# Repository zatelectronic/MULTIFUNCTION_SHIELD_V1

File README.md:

<div align="center">

# MULTIFUNCTION SHIELD V1

**Shield multifuncional para Arduino Uno com LEDs, botões, buzzer, potenciômetro, LDR, conector I2C e borne de terminais — tudo em uma única placa de expansão**

</div>

---

## 📋 Índice

- [MULTIFUNCTION SHIELD V1](#multifunction-shield-v1)
  - [📋 Índice](#-índice)
  - [Visão Geral](#visão-geral)
  - [Renders 3D](#renders-3d)
  - [Funcionalidades](#funcionalidades)
  - [Mapa de Pinos](#mapa-de-pinos)
  - [Especificações Técnicas](#especificações-técnicas)
  - [Lista de Materiais](#lista-de-materiais)
  - [Aplicações](#aplicações)
  - [Estrutura do Repositório](#estrutura-do-repositório)
  - [Como Usar](#como-usar)
    - [Instalação](#instalação)
    - [Exemplo — Piscar os 4 LEDs em sequência](#exemplo--piscar-os-4-leds-em-sequência)
    - [Exemplo — Leitura do potenciômetro e LDR](#exemplo--leitura-do-potenciômetro-e-ldr)
    - [Exemplo — Botões com pull-down](#exemplo--botões-com-pull-down)
  - [Sobre](#sobre)

---

## Visão Geral

**MULTIFUNCTION SHIELD V1** é uma placa de expansão (shield) para **Arduino Uno R3**, projetada pela **ZAT ELECTRONIC** utilizando **KiCad 10**. O shield encaixa diretamente nos conectores do Arduino e disponibiliza um conjunto completo de periféricos prontos para uso imediato em projetos de aprendizado, prototipagem e experimentos com eletrônica e programação.

Em uma única placa são integrados: **4 LEDs coloridos**, **4 botões tácteis**, **1 buzzer**, **1 potenciômetro**, **1 sensor LDR**, **1 conector I2C** (GND / VCC / SDA / SCL) e **1 borne de terminais** — cobrindo as principais necessidades de entrada e saída para projetos com Arduino.

> 💡 Ideal para aulas, workshops, laboratórios maker e iniciantes em eletrônica e programação com Arduino.

---

## Renders 3D

<div align="center">

*Vista superior — LEDs coloridos, botões tácteis, buzzer, potenciômetro e LDR*

<br/>

*Vista isométrica frontal — pinout Arduino Uno R3 e conector I2C*

<br/>

*Vista isométrica traseira — borne de terminais, pinos analógicos e digitais*

</div>

---

## Funcionalidades

- ✅ **4 LEDs 5mm PTH** — azul (LED1), vermelho (LED2), verde (LED3) e amarelo (LED4)
- ✅ **4 botões tácteis** (SW1–SW4) — 6×6×5mm PTH, com resistores pull-up 10KΩ (ativos em nível baixo)
- ✅ **1 buzzer PTH** (BZ1) — sinalização sonora ativa
- ✅ **1 potenciômetro 10KΩ** (RV1) — entrada analógica ajustável
- ✅ **1 sensor LDR** (R2) — leitura de luminosidade ambiente (divisor com R1 10KΩ)
- ✅ **1 conector I2C** (J2 — 4 pinos: GND / VCC / SDA / SCL) — expansão para displays, sensores e módulos I2C
- ✅ **1 borne de terminais KRE 3 pinos** (J1 — D11 / D12 / GND) — conexão externa por parafuso
- ✅ **Resistores de proteção 220Ω** (R7–R11) — para os LEDs e buzzer
- ✅ **Resistores pull-up 10KΩ** (R1, R3–R6) — para LDR e botões
- ✅ **Encaixe direto** no Arduino Uno R3 — sem soldagem adicional no Arduino
- ✅ **Todos os componentes PTH** — montagem manual simples
- ✅ **Made in Brazil** — serigrafia na PCB

---

## Mapa de Pinos

| Periférico | Pino Arduino | Descrição |
|------------|-------------|-----------|
| **LED1** — LED Azul | D2 | Saída digital |
| **LED2** — LED Vermelho | D3 | Saída digital (PWM) |
| **LED3** — LED Verde | D4 | Saída digital |
| **LED4** — LED Amarelo | D5 | Saída digital (PWM) |
| **SW1** — Botão 1 | D6 | Entrada digital (LOW = pressionado) |
| **SW2** — Botão 2 | D7 | Entrada digital (LOW = pressionado) |
| **SW3** — Botão 3 | D8 | Entrada digital (LOW = pressionado) |
| **SW4** — Botão 4 | D9 | Entrada digital (LOW = pressionado) |
| **BZ1** — Buzzer | D10 | Saída digital (PWM) |
| **RV1** — Potenciômetro | A0 | Entrada analógica |
| **R2** — Sensor de luz (LDR) | A1 | Entrada analógica |
| **J2 SDA** — I2C Dados | A4 (SDA) | Comunicação I2C |
| **J2 SCL** — I2C Clock | A5 (SCL) | Comunicação I2C |
| **J1** — Borne | D11 / D12 / GND | Terminal externo |

---

## Especificações Técnicas

| Parâmetro | Valor |
|-----------|-------|
| **Compatibilidade** | Arduino Uno R3 (encaixe direto) |
| **LEDs** | 4x 5mm PTH — azul, vermelho, verde, amarelo |
| **Botões** | 4x tácteis 6×6×5mm PTH |
| **Buzzer** | 1x PTH ativo |
| **Potenciômetro** | 1x 10KΩ PTH |
| **Sensor de Luz** | 1x LDR PTH |
| **Conector I2C** | 1x header 4 pinos 2,54mm (GND / VCC / SDA / SCL) |
| **Borne de Terminais** | 1x KRE 3 pinos, passo 5,0mm (D11 / D12 / GND) |
| **Resistores LEDs/Buzzer** | 220Ω — R7, R8, R9, R10, R11 |
| **Resistores Pull-up** | 10KΩ — R1 (LDR), R3, R4, R5, R6 (botões) |
| **Tensão de operação** | 5V (alimentado pelo Arduino) |
| **Tipo de montagem** | PTH — Através-furo |
| **Ferramenta de Projeto** | KiCad 10 |
| **Versão** | V1 — 2025 |

---

## Lista de Materiais

| Ref | Componente | Valor / Cor | Encapsulamento |
|-----|-----------|------------|----------------|
| A1 | Arduino Uno R3 | — | Shield (encaixe) |
| LED1 | LED 5mm | Azul | PTH 5mm |
| LED2 | LED 5mm | Vermelho | PTH 5mm |
| LED3 | LED 5mm | Verde | PTH 5mm |
| LED4 | LED 5mm | Amarelo | PTH 5mm |
| SW1–SW4 | Botão Táctil | 6×6×5mm | PTH |
| BZ1 | Buzzer | Ativo | PTH |
| RV1 | Potenciômetro | 10KΩ | PTH |
| R2 | Sensor de Luz (LDR) | LDR 5mm | PTH Vertical |
| J1 | Borne de Terminais | D11 / D12 / GND | KRE 3 pinos 5,0mm |
| J2 | Conector I2C | GND / VCC / SDA / SCL | Header 4 pinos 2,54mm |
| R7, R8, R9, R10, R11 | Resistor de proteção | 220Ω | Axial DIN0204 PTH |
| R1, R3, R4, R5, R6 | Resistor pull-up | 10KΩ | Axial DIN0204 PTH |

---

## Aplicações

- 🎓 **Ensino de eletrônica e programação** — plataforma completa para aprender Arduino do zero
- 🔬 **Prototipagem rápida** — periféricos prontos sem necessidade de protoboard
- 🏫 **Laboratórios maker e escolas técnicas** — kit de experimentos em uma única placa
- 🎮 **Projetos interativos** — jogos, quizzes e desafios com LEDs e botões
- 📡 **Integração com módulos I2C** — displays OLED, sensores de temperatura, RTC, etc.
- 🔊 **Projetos sonoros** — alarmes, melodias e sinalizações com buzzer
- 🌅 **Automação com luz** — controle baseado em luminosidade via LDR

---

## Estrutura do Repositório

```
MULTIFUNCTION_SHIELD_V1/
├── MULTIFUNCTION_SHIELD_V1.kicad_pro        # Arquivo de projeto KiCad
├── MULTIFUNCTION_SHIELD_V1.kicad_sch        # Esquemático: capa A2 + folhas ARDUINO / ENTRADAS / SAIDAS (KiCad 10)
├── MULTIFUNCTION_SHIELD_V1.kicad_pcb        # Layout da PCB (KiCad 10)
├── MULTIFUNCTION_SHIELD_V1.kicad_prl        # Configurações locais
├── packages3D/                              # Modelos 3D arquivados
│   ├── LED 5mm Blue.step
│   ├── LED 5mm Red.step
│   ├── LED 5mm Green.step
│   ├── LED 5mm Yellow.step
│   ├── SW_PUSH_6mm_H5mm.wrl
│   ├── Buzzer_12x9.5RM7.6.wrl
│   ├── Rez10K.stp
│   ├── R_LDR_5.1x4.3mm_P3.4mm_Vertical.wrl
│   ├── DG306-5.0-03P-12-00AH.STEP
│   ├── PinHeader_1x04_P2.54mm_Vertical.wrl
│   ├── SIL_Socket06_.stp
│   ├── SIL_Socket08_.stp
│   ├── SIL_Socket10_.stp
│   └── Resistor Axial 0.5W *.STEP
├── fp-info-cache                            # Cache de footprints
├── imagem_1.png                             # Render 3D superior
├── imagem_2.png                             # Render 3D isométrico frontal
├── imagem_3.png                             # Render 3D isométrico traseiro
└── README.md
```

---

## Como Usar

### Instalação

1. Encaixe o **MULTIFUNCTION SHIELD V1** diretamente nos conectores do Arduino Uno R3
2. Conecte o Arduino ao computador via USB
3. Abra a **Arduino IDE** ou **PlatformIO** e selecione a placa **Arduino Uno**
4. Carregue seu sketch e comece a experimentar

### Exemplo — Piscar os 4 LEDs em sequência

```cpp
#define LED_AZUL    2
#define LED_VERMELHO 3
#define LED_VERDE   4
#define LED_AMARELO 5

void setup() {
  pinMode(LED_AZUL,     OUTPUT);
  pinMode(LED_VERMELHO, OUTPUT);
  pinMode(LED_VERDE,    OUTPUT);
  pinMode(LED_AMARELO,  OUTPUT);
}

void loop() {
  digitalWrite(LED_AZUL, HIGH);    delay(300);
  digitalWrite(LED_AZUL, LOW);
  digitalWrite(LED_VERMELHO, HIGH); delay(300);
  digitalWrite(LED_VERMELHO, LOW);
  digitalWrite(LED_VERDE, HIGH);   delay(300);
  digitalWrite(LED_VERDE, LOW);
  digitalWrite(LED_AMARELO, HIGH); delay(300);
  digitalWrite(LED_AMARELO, LOW);
}
```

### Exemplo — Leitura do potenciômetro e LDR

```cpp
void setup() {
  Serial.begin(9600);
}

void loop() {
  int pot = analogRead(A0); // potenciômetro
  int ldr = analogRead(A1); // sensor de luz
  Serial.print("POT: "); Serial.print(pot);
  Serial.print(" | LDR: "); Serial.println(ldr);
  delay(500);
}
```

### Exemplo — Botões com pull-up (pressionado = LOW)

```cpp
#define BTN1 6
#define BTN2 7
#define BTN3 8
#define BTN4 9
#define BUZZER 10

void setup() {
  pinMode(BTN1, INPUT);
  pinMode(BTN2, INPUT);
  pinMode(BTN3, INPUT);
  pinMode(BTN4, INPUT);
  pinMode(BUZZER, OUTPUT);
}

void loop() {
  if (digitalRead(BTN1) == LOW) {
    tone(BUZZER, 1000, 200); // aciona buzzer ao pressionar SW1
  }
}
```

## Sobre

<div align="center">

Projetado por **ZAT ELECTRONIC**

*MULTIFUNCTION SHIELD V1 — 2025 — Made in Brazil 🇧🇷*

</div>

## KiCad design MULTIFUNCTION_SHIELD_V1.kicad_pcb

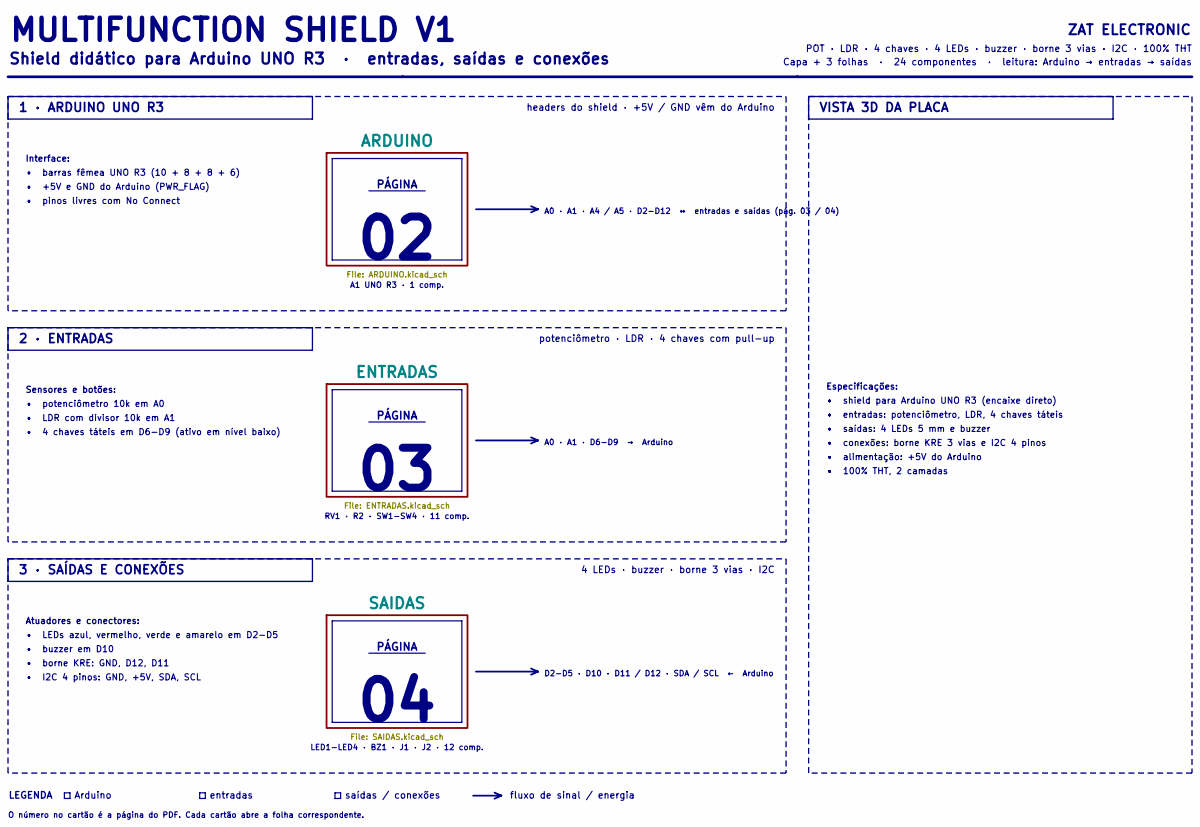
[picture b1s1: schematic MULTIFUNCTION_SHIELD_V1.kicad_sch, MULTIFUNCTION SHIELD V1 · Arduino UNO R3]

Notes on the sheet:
• saídas: 4 LEDs 5 mm e buzzer
headers do shield · +5V / GND vêm do Arduino
LED1-LED4 · BZ1 · J1 · J2 · 12 comp.
3 · SAÍDAS E CONEXÕES
potenciômetro · LDR · 4 chaves com pull-up
Arduino
• barras fêmea UNO R3 (10 + 8 + 8 + 6)
2 · ENTRADAS
• conexões: borne KRE 3 vias e I2C 4 pinos
PÁGINA
• alimentação: +5V do Arduino
saídas / conexões
Capa + 3 folhas · 24 componentes · leitura: Arduino → entradas → saídas
4 LEDs · buzzer · borne 3 vias · I2C
entradas
POT · LDR · 4 chaves · 4 LEDs · buzzer · borne 3 vias · I2C · 100% THT
LEGENDA
1 · ARDUINO UNO R3
• pinos livres com No Connect
• 100% THT, 2 camadas
• buzzer em D10
Especificações:
Shield didático para Arduino UNO R3 · entradas, saídas e conexões
• borne KRE: GND, D12, D11
VISTA 3D DA PLACA
A0 · A1 · D6-D9 → Arduino
• shield para Arduino UNO R3 (encaixe direto)
MULTIFUNCTION SHIELD V1
A1 UNO R3 · 1 comp.
Atuadores e conectores:
A0 · A1 · A4 / A5 · D2-D12 ↔ entradas e saídas (pág. 03 / 04)
• LEDs azul, vermelho, verde e amarelo em D2-D5
• I2C 4 pinos: GND, +5V, SDA, SCL
O número no cartão é a página do PDF. Cada cartão abre a folha correspondente.
• +5V e GND do Arduino (PWR_FLAG)
• entradas: potenciômetro, LDR, 4 chaves táteis
• LDR com divisor 10k em A1
• 4 chaves táteis em D6-D9 (ativo em nível baixo)
fluxo de sinal / energia
D2-D5 · D10 · D11 / D12 · SDA / SCL ← Arduino

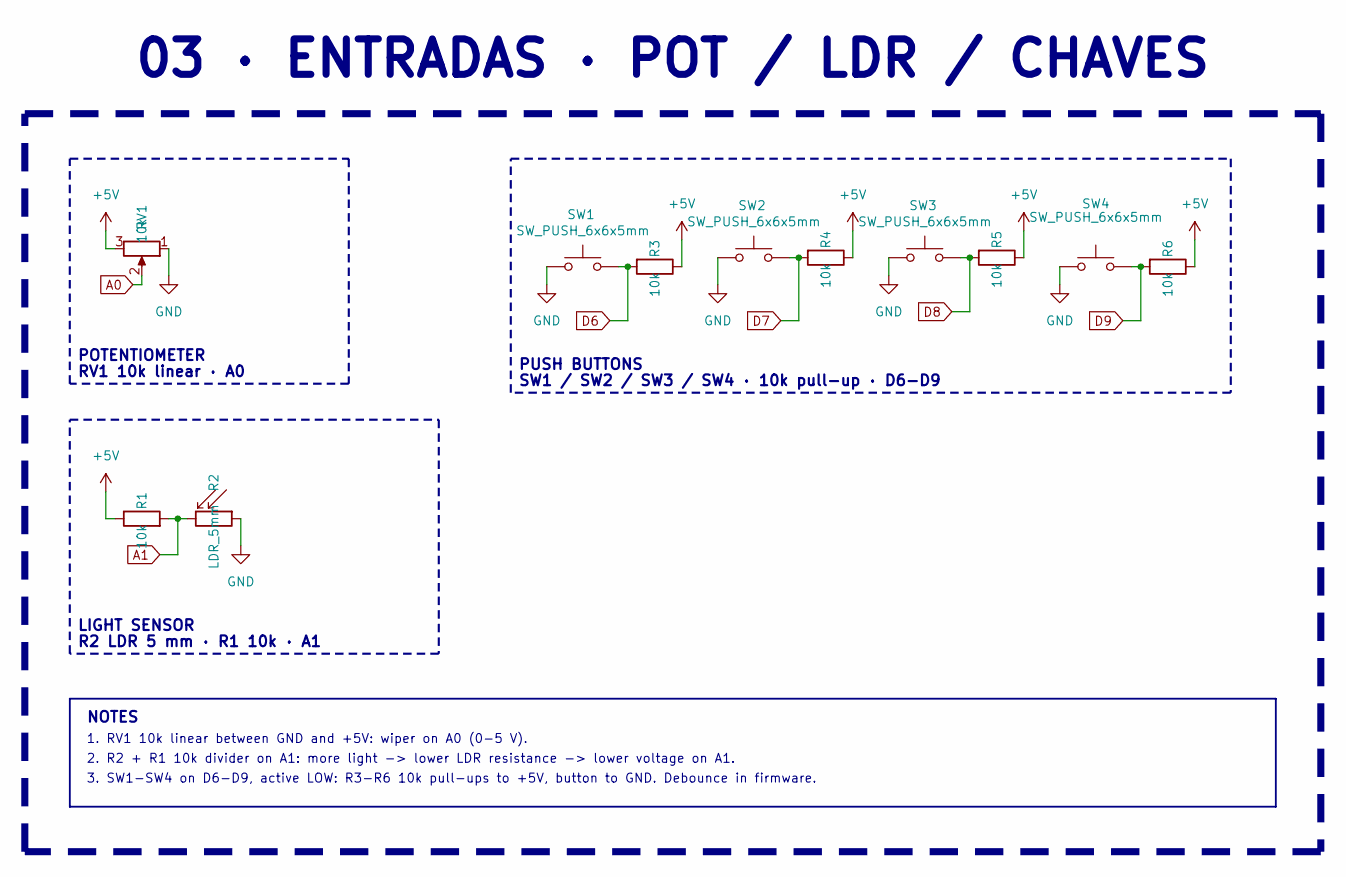
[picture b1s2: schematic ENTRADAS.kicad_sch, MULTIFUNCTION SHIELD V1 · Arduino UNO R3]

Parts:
R1, R3, R4, R5, R6: 10k; R_Axial_DIN0204_L3.6mm_D1.6mm_P7.62mm_Horizontal_10K
R2: LDR_5mm; R_LDR_5.1x4.3mm_P3.4mm_Vertical
RV1: 10k; Potentiometer_Piher_T-16H_Single_Horizontal_10K_EdgeMount
SW1, SW2, SW3, SW4: SW_PUSH_6x6x5mm; SW_PUSH_6mm_H5mm

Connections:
+5V: R1.1, R3.1, R4.1, R5.1, R6.1, RV1.3; also elsewhere on the board
A0: RV1.2; also elsewhere on the board
A1: R1.2, R2.2; also elsewhere on the board
D6: R3.2, SW1.2; also elsewhere on the board
D7: R4.2, SW2.2; also elsewhere on the board
D8: R5.2, SW3.2; also elsewhere on the board
D9: R6.2, SW4.2; also elsewhere on the board
GND: R2.1, RV1.1, SW1.1, SW2.1, SW3.1, SW4.1; also elsewhere on the board

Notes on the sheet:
1. RV1 10k linear between GND and +5V: wiper on A0 (0-5 V).
03 · ENTRADAS · POT / LDR / CHAVES
LIGHT SENSOR
R2 LDR 5 mm · R1 10k · A1
POTENTIOMETER
NOTES
PUSH BUTTONS
RV1 10k linear · A0
SW1 / SW2 / SW3 / SW4 · 10k pull-up · D6-D9
2. R2 + R1 10k divider on A1: more light -> lower LDR resistance -> lower voltage on A1.
3. SW1-SW4 on D6-D9, active LOW: R3-R6 10k pull-ups to +5V, button to GND. Debounce in firmware.

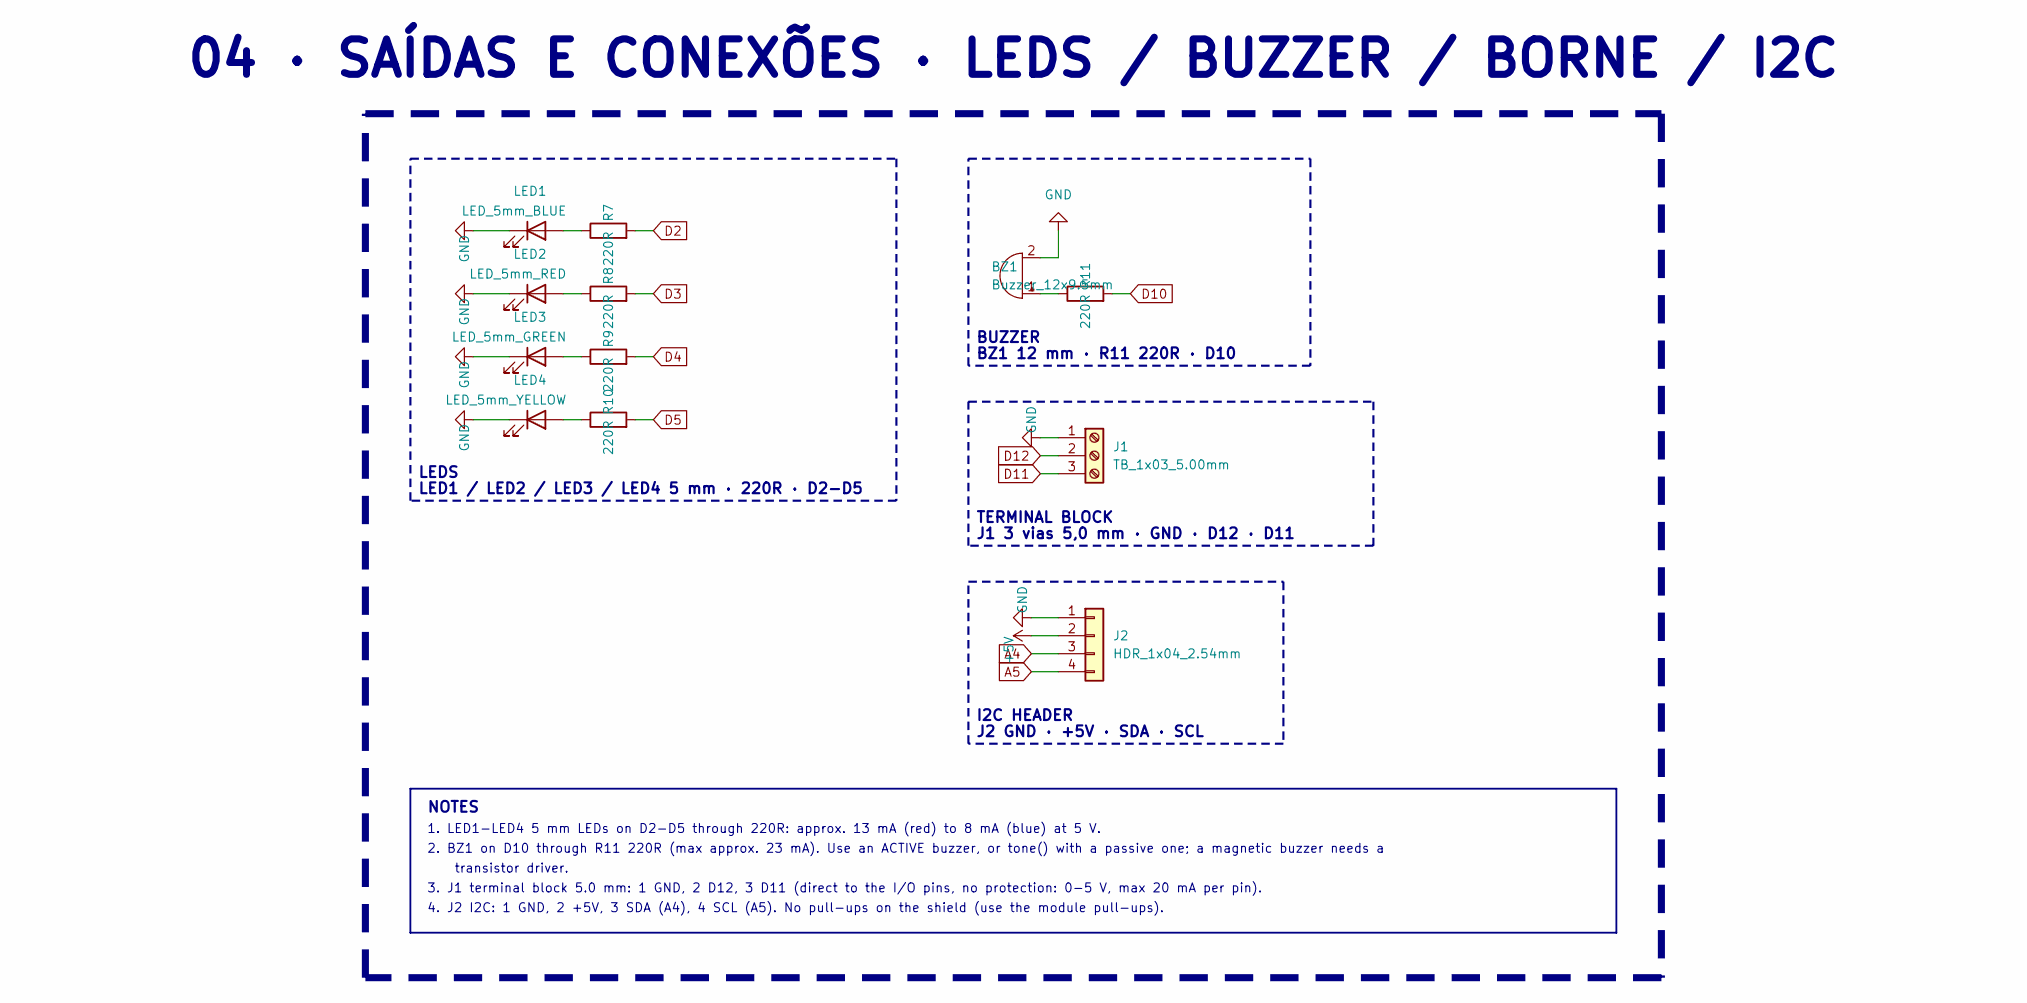
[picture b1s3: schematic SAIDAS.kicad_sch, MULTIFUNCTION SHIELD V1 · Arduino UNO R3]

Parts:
BZ1: Buzzer_12x9.5mm; Buzzer_12x9.5RM7.6
J1: TB_1x03_5.00mm; TerminalBlock_MaiXu_MX126-5.0-03P_1x03_P5.00mm_DG306
J2: HDR_1x04_2.54mm; PinHeader_1x04_P2.54mm_Vertical
LED1: LED_5mm_BLUE; LED_D5.0mm_Blue
LED2: LED_5mm_RED; LED_D5.0mm_Red
LED3: LED_5mm_GREEN; LED_D5.0mm_Green
LED4: LED_5mm_YELLOW; LED_D5.0mm_Yellow
R7, R8, R9, R10, R11: 220R; R_Axial_DIN0204_L3.6mm_D1.6mm_P7.62mm_Horizontal_220R

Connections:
+5V: J2.2; also elsewhere on the board
A4: J2.3; also elsewhere on the board
A5: J2.4; also elsewhere on the board
D2: R7.2; also elsewhere on the board
D3: R8.2; also elsewhere on the board
D4: R9.2; also elsewhere on the board
D5: R10.2; also elsewhere on the board
D10: R11.2; also elsewhere on the board
D11: J1.3; also elsewhere on the board
D12: J1.2; also elsewhere on the board
GND: BZ1.2 (-), J1.1, J2.1, LED1.1 (K), LED2.1 (K), LED3.1 (K), LED4.1 (K); also elsewhere on the board
unnamed: BZ1.1 (+), R11.1
unnamed: LED1.2 (A), R7.1
unnamed: LED2.2 (A), R8.1
unnamed: LED3.2 (A), R9.1
unnamed: LED4.2 (A), R10.1

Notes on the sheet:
J2 GND · +5V · SDA · SCL
TERMINAL BLOCK
BZ1 12 mm · R11 220R · D10
3. J1 terminal block 5.0 mm: 1 GND, 2 D12, 3 D11 (direct to the I/O pins, no protection: 0-5 V, max 20 mA per pin).
2. BZ1 on D10 through R11 220R (max approx. 23 mA). Use an ACTIVE buzzer, or tone() with a passive one; a magnetic buzzer needs a
I2C HEADER
4. J2 I2C: 1 GND, 2 +5V, 3 SDA (A4), 4 SCL (A5). No pull-ups on the shield (use the module pull-ups).
LED1 / LED2 / LED3 / LED4 5 mm · 220R · D2-D5
transistor driver.
J1 3 vias 5,0 mm · GND · D12 · D11
LEDS
BUZZER
NOTES
1. LED1-LED4 5 mm LEDs on D2-D5 through 220R: approx. 13 mA (red) to 8 mA (blue) at 5 V.
04 · SAÍDAS E CONEXÕES · LEDS / BUZZER / BORNE / I2C

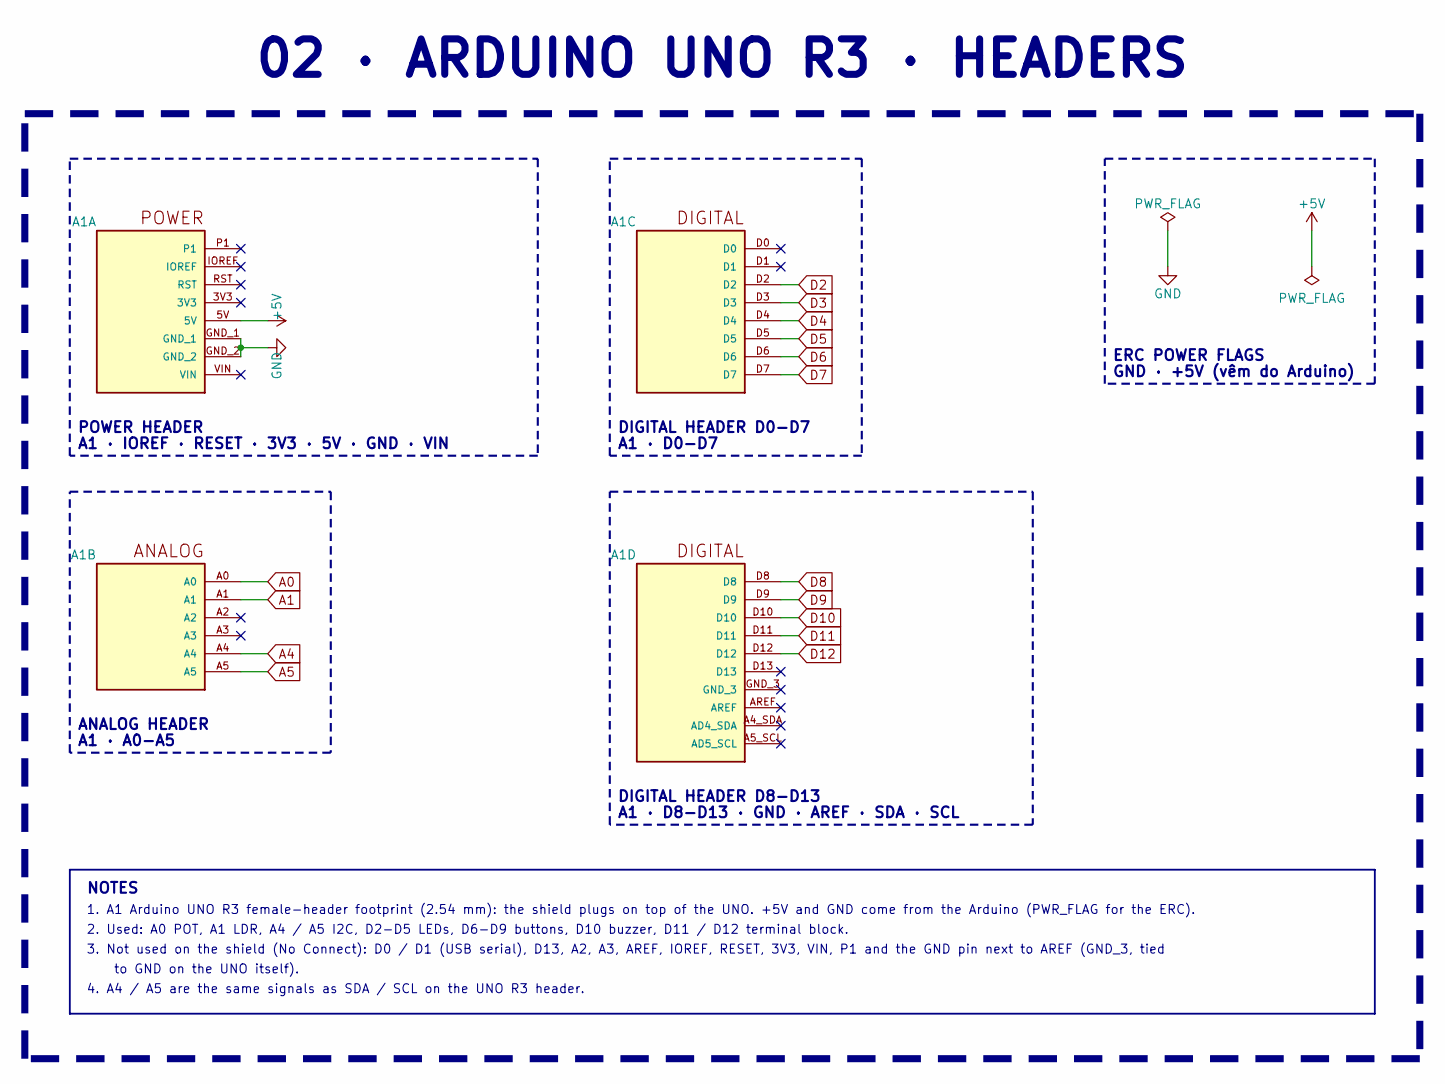
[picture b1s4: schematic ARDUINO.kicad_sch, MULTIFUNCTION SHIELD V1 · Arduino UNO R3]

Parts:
A1: ARDUINO_UNO_R3_Headers

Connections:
+5V: A1.5V; also elsewhere on the board
A0: A1.A0; also elsewhere on the board
A1: A1.A1; also elsewhere on the board
A4: A1.A4; also elsewhere on the board
A5: A1.A5; also elsewhere on the board
D2: A1.D2; also elsewhere on the board
D3: A1.D3; also elsewhere on the board
D4: A1.D4; also elsewhere on the board
D5: A1.D5; also elsewhere on the board
D6: A1.D6; also elsewhere on the board
D7: A1.D7; also elsewhere on the board
D8: A1.D8; also elsewhere on the board
D9: A1.D9; also elsewhere on the board
D10: A1.D10; also elsewhere on the board
D11: A1.D11; also elsewhere on the board
D12: A1.D12; also elsewhere on the board
GND: A1.GND_1, A1.GND_2; also elsewhere on the board

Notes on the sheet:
A1 · A0-A5
A1 · D0-D7
GND · +5V (vêm do Arduino)
DIGITAL HEADER D0-D7
POWER HEADER
ANALOG HEADER
to GND on the UNO itself).
2. Used: A0 POT, A1 LDR, A4 / A5 I2C, D2-D5 LEDs, D6-D9 buttons, D10 buzzer, D11 / D12 terminal block.
A1 · IOREF · RESET · 3V3 · 5V · GND · VIN
NOTES
1. A1 Arduino UNO R3 female-header footprint (2.54 mm): the shield plugs on top of the UNO. +5V and GND come from the Arduino (PWR_FLAG for the ERC).
DIGITAL HEADER D8-D13
ERC POWER FLAGS
4. A4 / A5 are the same signals as SDA / SCL on the UNO R3 header.
02 · ARDUINO UNO R3 · HEADERS
A1 · D8-D13 · GND · AREF · SDA · SCL
3. Not used on the shield (No Connect): D0 / D1 (USB serial), D13, A2, A3, AREF, IOREF, RESET, 3V3, VIN, P1 and the GND pin next to AREF (GND_3, tied

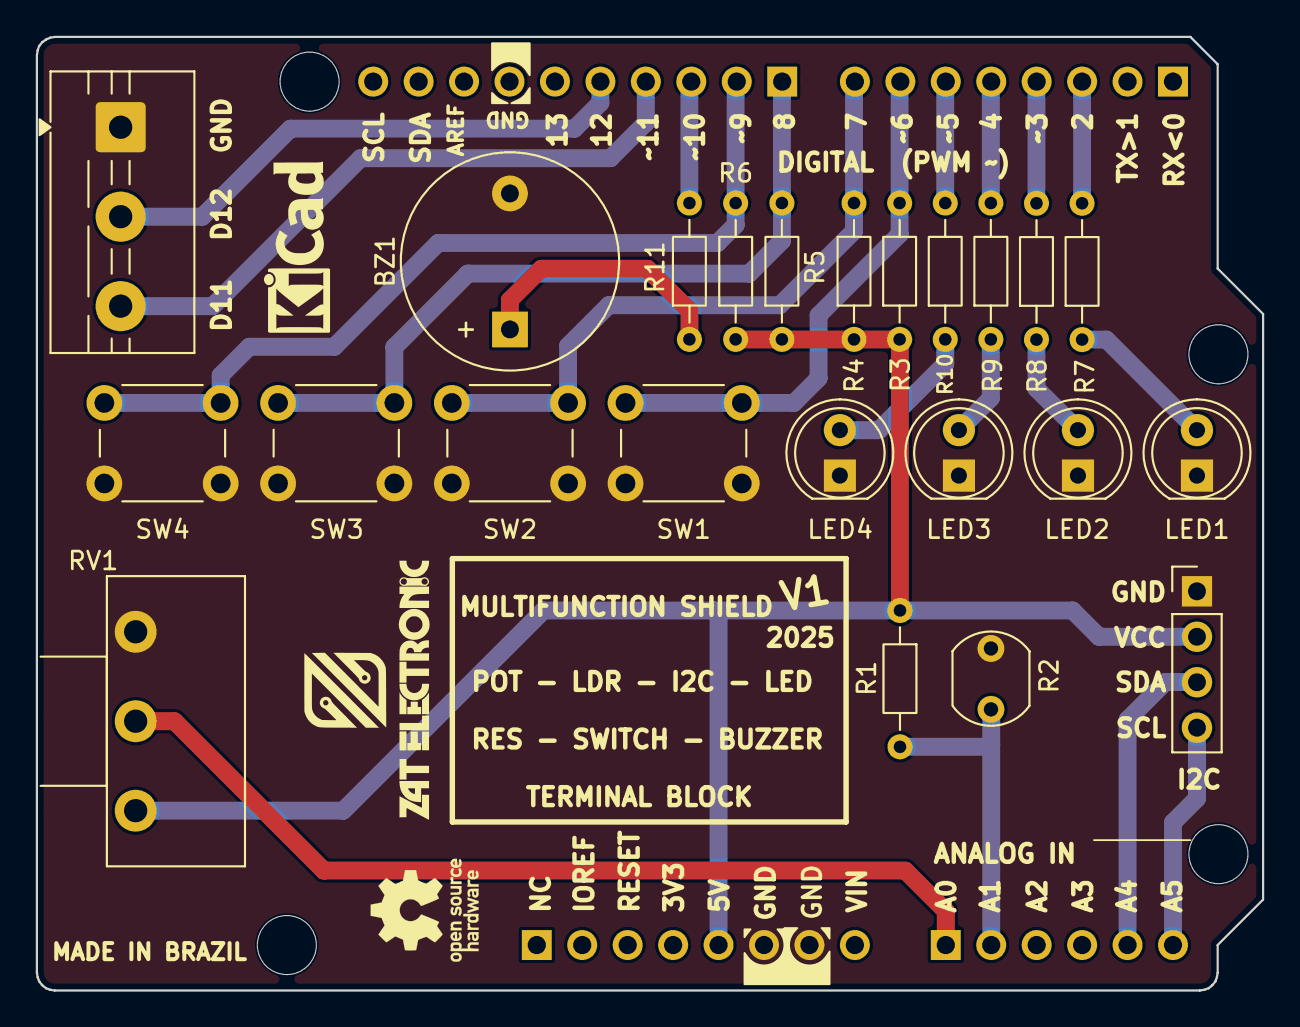
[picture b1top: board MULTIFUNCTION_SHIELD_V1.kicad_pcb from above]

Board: 2 copper layers, 68.5 x 53.3 mm, 24 parts (0 on the bottom side), 22 nets.

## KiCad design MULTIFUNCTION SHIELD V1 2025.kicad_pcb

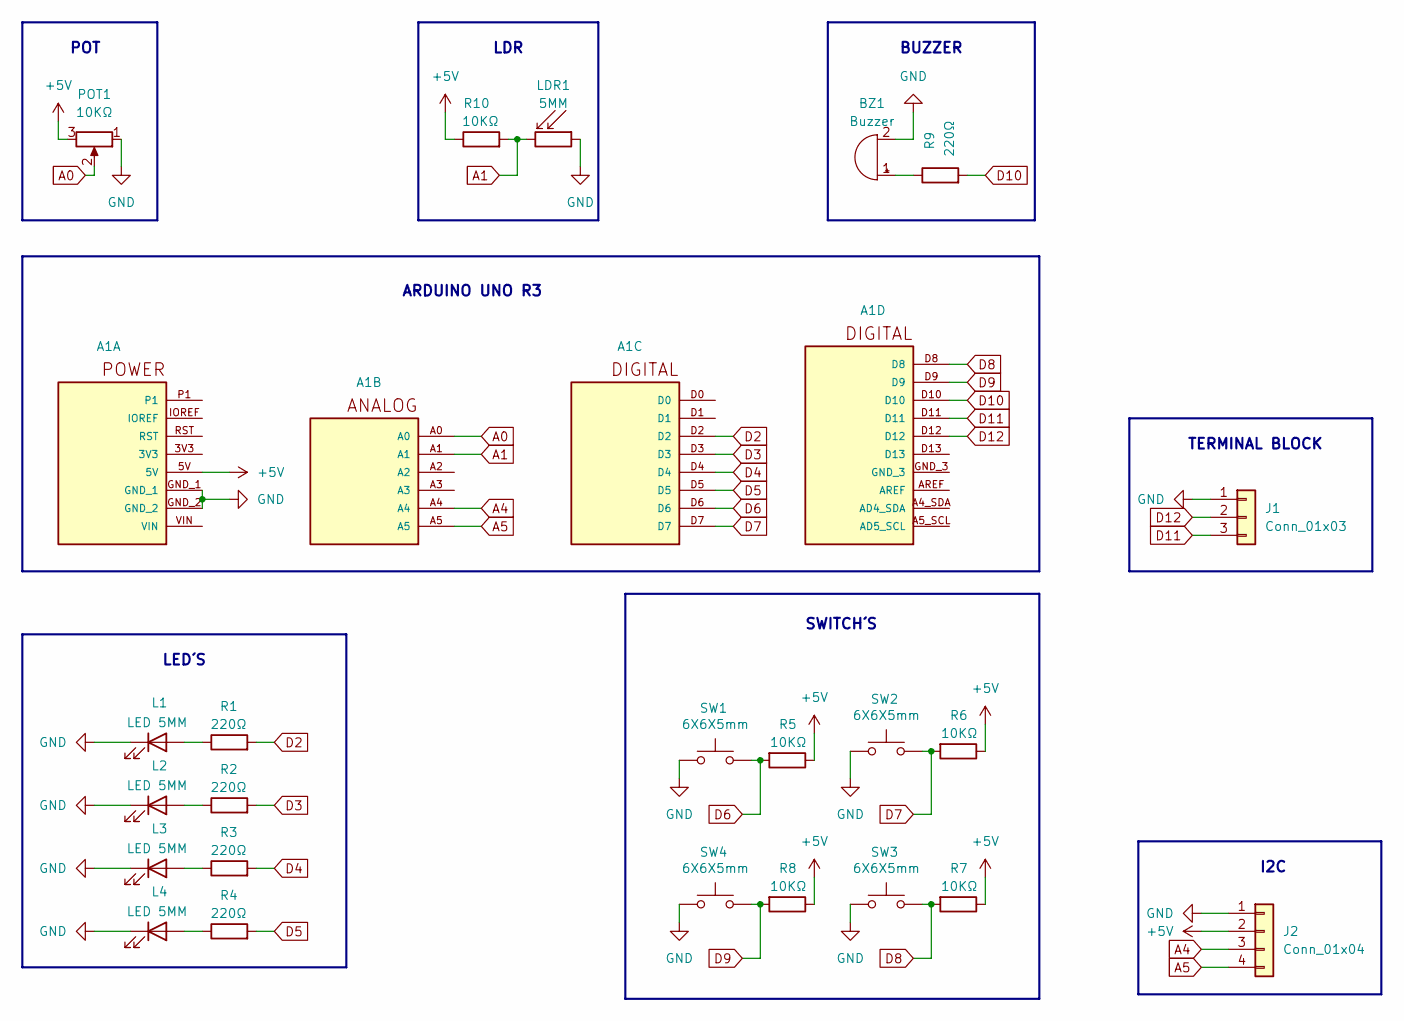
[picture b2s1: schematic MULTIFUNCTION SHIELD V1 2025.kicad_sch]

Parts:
A1: ARDUINO_UNO_REV3; ARDUINO_ARDUINO_UNO_REV3; PARTREV N/A
BZ1: Buzzer; Buzzer_12x9.5RM7.6
J1: Conn_01x03; TerminalBlock_MaiXu_MX126-5.0-03P_1x03_P5.00mm
J2: Conn_01x04; PinHeader_1x04_P2.54mm_Vertical
L1, L2, L3, L4: LED 5MM; LED_D5.0mm
LDR1: 5MM; R_LDR_5.1x4.3mm_P3.4mm_Vertical
POT1: 10KΩ; Potentiometer_Piher_T-16H_Single_Horizontal
R1, R2, R3, R4, R9: 220Ω; R_Axial_DIN0204_L3.6mm_D1.6mm_P7.62mm_Horizontal
R5, R6, R7, R8, R10: 10KΩ; R_Axial_DIN0204_L3.6mm_D1.6mm_P7.62mm_Horizontal
SW1, SW2, SW3, SW4: 6X6X5mm; SW_PUSH_6mm_H5mm

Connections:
+5V: A1.5V, J2.2, POT1.3, R5.1, R6.1, R7.1, R8.1, R10.1
A0: A1.A0, POT1.2
A1: A1.A1, LDR1.2, R10.2
A4: A1.A4, J2.3
A5: A1.A5, J2.4
D2: A1.D2, R1.2
D3: A1.D3, R2.2
D4: A1.D4, R3.2
D5: A1.D5, R4.2
D6: A1.D6, R5.2, SW1.2
D7: A1.D7, R6.2, SW2.2
D8: A1.D8, R7.2, SW3.2
D9: A1.D9, R8.2, SW4.2
D10: A1.D10, R9.2
D11: A1.D11, J1.3
D12: A1.D12, J1.2
GND: A1.GND_1, A1.GND_2, BZ1.2 (-), J1.1, J2.1, L1.1 (K), L2.1 (K), L3.1 (K), L4.1 (K), LDR1.1, POT1.1, SW1.1, SW2.1, SW3.1, SW4.1
unnamed: BZ1.1 (+), R9.1
unnamed: L1.2 (A), R1.1
unnamed: L2.2 (A), R2.1
unnamed: L3.2 (A), R3.1
unnamed: L4.2 (A), R4.1

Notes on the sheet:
LED´S
SWITCH´S
LDR
BUZZER
I2C
TERMINAL BLOCK
POT
ARDUINO UNO R3

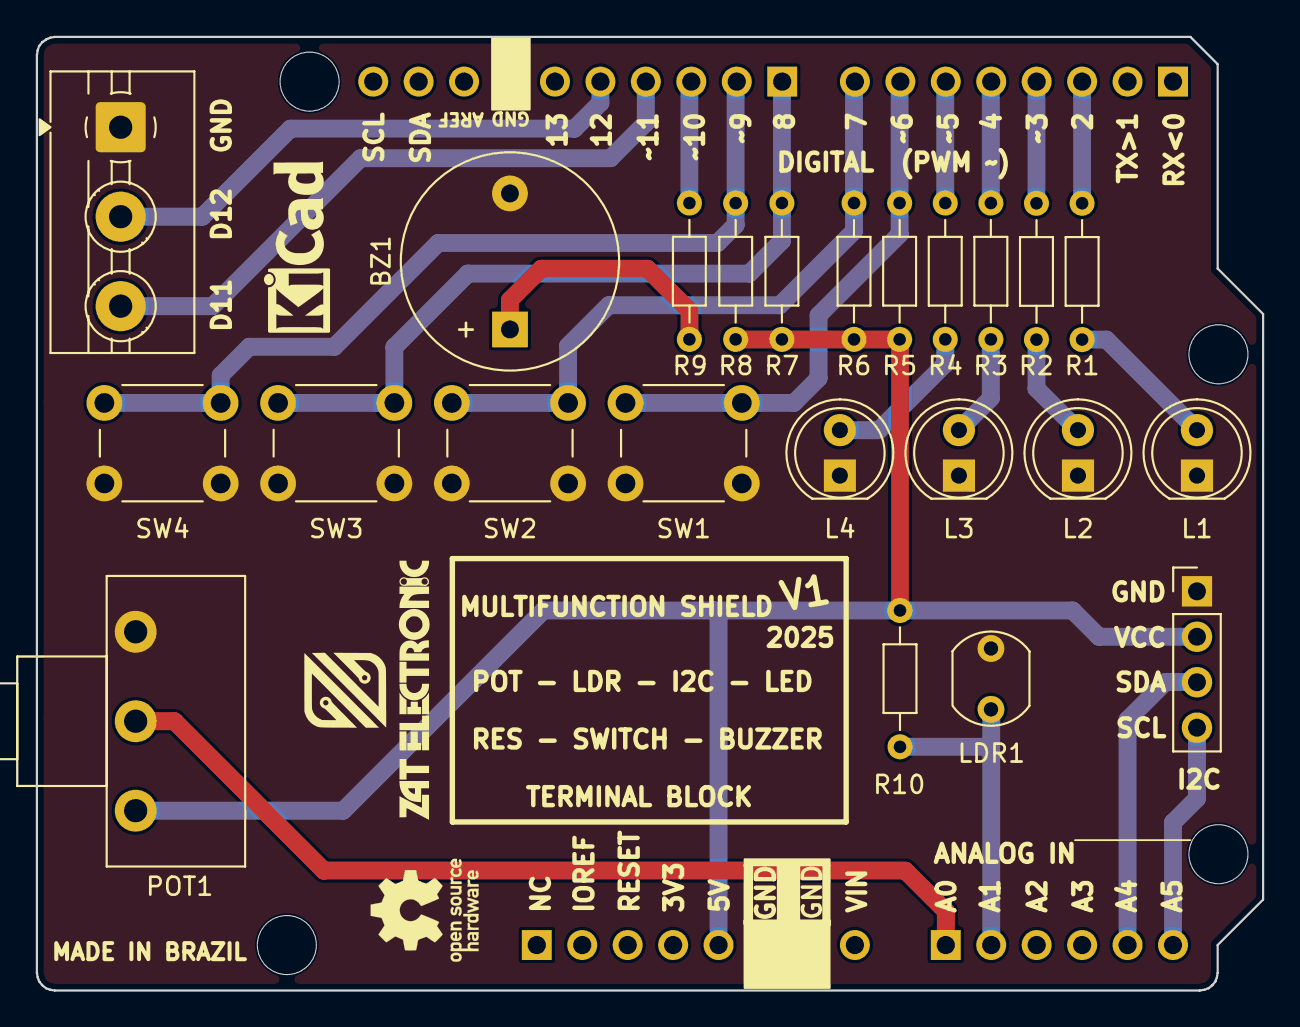
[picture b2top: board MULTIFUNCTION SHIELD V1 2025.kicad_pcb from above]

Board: 2 copper layers, 68.5 x 53.3 mm, 24 parts (0 on the bottom side), 22 nets.

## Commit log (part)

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2026-06-28 commit_3
2026-06-29 COMMIT-4
